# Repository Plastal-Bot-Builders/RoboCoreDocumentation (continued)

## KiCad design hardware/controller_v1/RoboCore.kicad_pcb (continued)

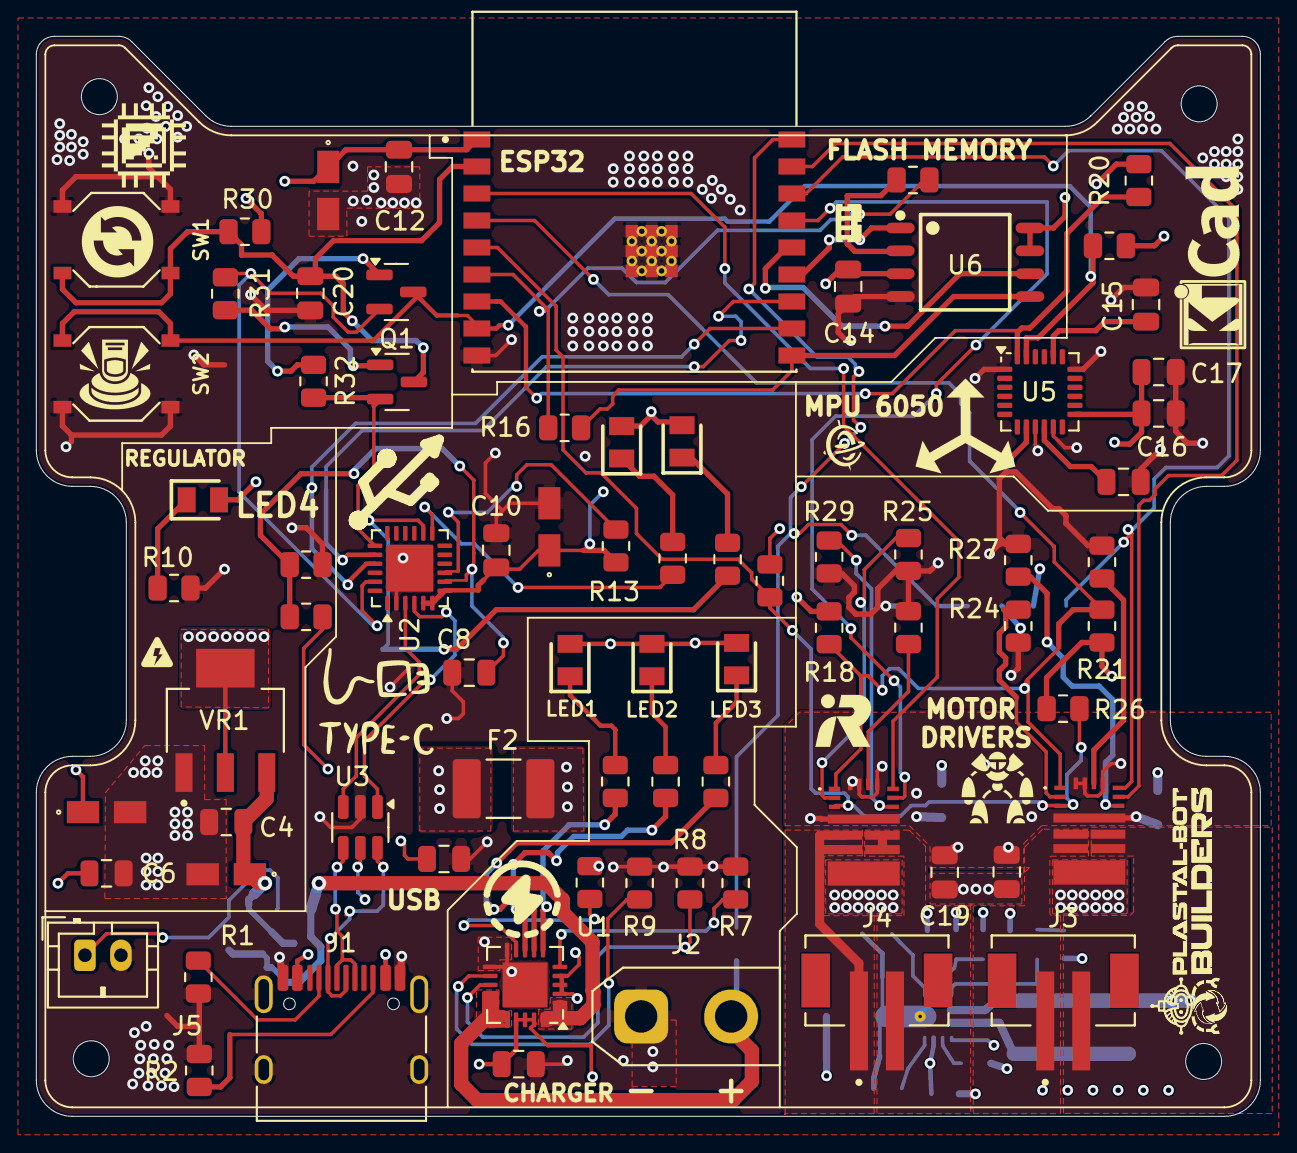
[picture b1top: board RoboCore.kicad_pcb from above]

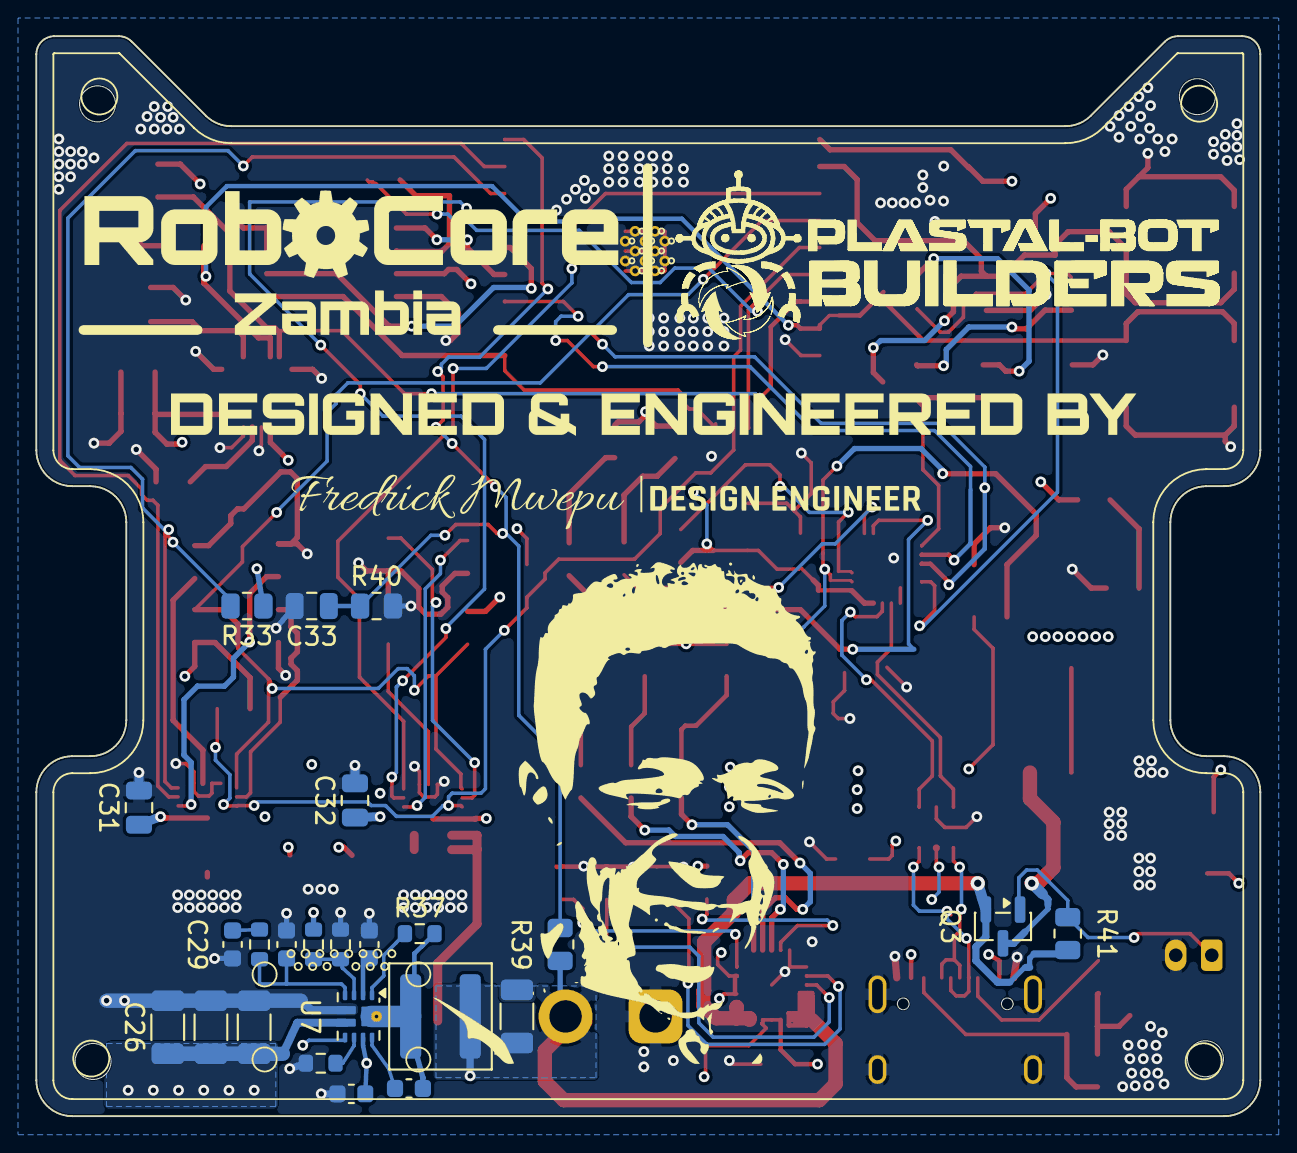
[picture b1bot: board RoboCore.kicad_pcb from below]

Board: 4 copper layers, 68.0 x 60.0 mm, 104 parts (24 on the bottom side), 73 nets.

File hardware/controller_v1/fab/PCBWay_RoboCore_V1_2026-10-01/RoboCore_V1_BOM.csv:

Item,Designators,Qty,Value,Package (KiCad footprint),Manufacturer,Manufacturer Part Number,Rating / sourcing note,Mount,Description
1,"C1,C4,C6,C10,C13,C31,C32,C33",8,0.1µF,C_0805_2012Metric,,,"MLCC X7R ±10%, 50 V",SMD,"capacitor, non-polarized/bipolar"
2,"C2,C8,C14,C20",4,1µF,C_0805_2012Metric,,,"MLCC X7R ±10%, 25 V (16 V min)",SMD,"capacitor, non-polarized/bipolar"
3,"C5,C7,C11",3,10µF,1206 (3216 metric) MLCC on T491A pads,,,"CERAMIC (not tantalum): MLCC 1206 X5R ±10%, 16 V, e.g. Samsung CL31A106KOHNNNE; the T491A footprint pads fit a 1206 part",SMD,Ceramic capacitor (MLCC) 1206 X5R 16V; fits the tantalum A-case (3216) pads
4,C9,1,4.7µF,1206 (3216 metric) MLCC on T491A pads,,,"CERAMIC (not tantalum): MLCC 1206 X5R ±10%, 16 V, e.g. Samsung CL31A475KOHNNNE; the T491A footprint pads fit a 1206 part",SMD,Ceramic capacitor (MLCC) 1206 X5R 16V; fits the tantalum A-case (3216) pads
5,C12,1,4.7µF,C_0805_2012Metric,,,"MLCC X5R/X7R ±10%, 16 V (10 V min)",SMD,"capacitor, non-polarized/bipolar"
6,C15,1,2.2nF,C_0805_2012Metric,,,"MLCC X7R ±10%, 50 V; MPU-6050 charge-pump capacitor, 50 V rating required by the datasheet",SMD,"capacitor, non-polarized/bipolar"
7,"C16,C17",2,2.2µF,C_0805_2012Metric,,,"MLCC X5R/X7R ±10%, 16 V (10 V min)",SMD,"capacitor, non-polarized/bipolar"
8,"C18,C19",2,22µF,C_0805_2012Metric,,,"MLCC X5R ±20%, 16 V; 6 V motor rail; e.g. Samsung CL21A226MOQNNNE",SMD,"capacitor, non-polarized/bipolar"
9,"C22,C24,C25,C26",4,22µF 16V,C_1206_3216Metric,,,"MLCC X5R/X7R, 16 V or higher (25 V keeps more capacitance at 6 V)",SMD,capacitor
10,"C23,C28",2,0.1µF,C_0603_1608Metric,,,"MLCC X7R ±10%, 25 V (16 V min)",SMD,capacitor
11,C27,1,2.2µF,C_0603_1608Metric,,,"MLCC X5R/X7R ±10%, 16 V",SMD,capacitor
12,C29,1,10nF,C_0603_1608Metric,,,"MLCC X7R ±10%, 50 V",SMD,capacitor
13,C30,1,22pF,C_0603_1608Metric,,,"MLCC C0G/NP0 ±5%, 50 V",SMD,capacitor
14,F2,1,Polyfuse,FUSSC324X455X250-2N,,,"PTC resettable fuse, 1812, I_hold 1.5 A, V_max ≥ 6 V, e.g. Bourns MF-MSMF150/24X-2 (MF-MSMF150-2 is obsolete)",SMD,"Resettable fuse, polymeric positive temperature coefficient"
15,"IC1,IC2",2,DRV8245HQRXZRQ1,DRV8245HQRXZRQ1,Texas Instruments,DRV8245HQRXZRQ1,,SMD,"Motor / Motion / Ignition Controllers & Drivers Automotive 40-V, 32-A H-Bridge driver with integrated current sensing and feedback"
16,J1,1,TYPE-C-31-M-12,USB_C_Receptacle_HRO_TYPE-C-31-M-12,Korean Hroparts Elec,TYPE-C-31-M-12,,SMD,"USB 2.0 Type-C receptacle, 16 pin, mid/top mount"
17,J2,1,XT30UPB-M,AMASS_XT30UPB-M_1x02_P5.0mm_Vertical,AMASS,XT30UPB-M,,THT,"Battery input, XT30 male, vertical PCB mount, keyed"
18,J3,1,MOTOR_A,JST_B2B-PH-SM4-TB,JST,B2B-PH-SM4-TB,,SMD,
19,J4,1,MOTOR_B,JST_B2B-PH-SM4-TB,JST,B2B-PH-SM4-TB,,SMD,
20,J5,1,POWER_SW,JST_PH_B2B-PH-K_1x02_P2.00mm_Vertical,JST,B2B-PH-K-S,,THT,External ON/OFF switch (closed = ON); fit a jumper for always-on
21,L1,1,2.2uH,L_Coilcraft_XAL5030-XXX,Coilcraft,XAL5030-222MEC,,SMD,"Boost inductor 2.2 uH, Isat 9.2 A, 14.5 mOhm max"
22,"LED1,LED4,LED6",3,LTST-C170KRKT,LEDC2012X120N,Lite-On,LTST-C170KRKT,,SMD,Standard LEDs - SMD Red Clear 631nm
23,"LED2,LED5",2,LTST-C170GKT,LEDC2012X120N,Lite-On,LTST-C170GKT,,SMD,"LED,SMD,0805,Green,6mcd,130deg Lite-On LTST-C170GKT, CHIPLED 0805 Series Green LED, 569 nm 2012 (0805), Rectangle Lens SMD package"
24,LED3,1,LTST-C170TBKT,LEDC2012X120N,Lite-On,LTST-C170TBKT,,SMD,"LED,SMD,0805,Blue,28mcd,130deg"
25,"Q1,Q2",2,BC817,SOT-23,Nexperia,BC817-40,any BC817 (-16/-25/-40) is fine,SMD,"0.8A Ic, 45V Vce, NPN Transistor, SOT-23"
26,Q3,1,AO3401A,SOT-23,Alpha & Omega,AO3401A,,SMD,Power switch P-MOSFET
27,"R1,R2",2,5.1K,R_0805_2012Metric,,,"Thick film 1%, 1/8 W",SMD,resistor
28,"R3,R4,R5,R10,R14,R15",6,470,R_0805_2012Metric,,,"Thick film 1%, 1/8 W",SMD,resistor
29,"R6,R7,R9,R18,R21,R26,R27,R28,R29,R30,R31,R32,R33",13,10K,R_0805_2012Metric,,,"Thick film 1%, 1/8 W",SMD,"Boot-strap pull-up: GPIO2/DIR_A must read high at reset (DRV824x input pull-down),resistor"
30,"R8,R13,R24,R25",4,1K,R_0805_2012Metric,,,"Thick film 1%, 1/8 W",SMD,resistor
31,R11,1,47K,R_0805_2012Metric,,,"Thick film 1%, 1/8 W",SMD,resistor
32,R12,1,22K,R_0805_2012Metric,,,"Thick film 1%, 1/8 W",SMD,resistor
33,R17,1,50,R_0805_2012Metric,,,"Thick film 1%, 1/8 W; 49.9 Ω acceptable",SMD,resistor
34,"R19,R20",2,4.7K,R_0805_2012Metric,,,"Thick film 1%, 1/8 W",SMD,resistor
35,"R22,R23",2,8.2K,R_0805_2012Metric,,,"Thick film 1%, 1/8 W",SMD,resistor
36,R34,1,9.1K,R_0603_1608Metric,,,Thick film 1% (boost loop compensation),SMD,resistor
37,"R35,R37",2,300K,R_0603_1608Metric,,,"Thick film 1% (sets boost output voltage, switching frequency and current limit; 1% required)",SMD,resistor
38,R36,1,75K,R_0603_1608Metric,,,"Thick film 1% (sets boost output voltage, switching frequency and current limit; 1% required)",SMD,resistor
39,R38,1,200K,R_0603_1608Metric,,,"Thick film 1% (sets boost output voltage, switching frequency and current limit; 1% required)",SMD,resistor
40,"R39,R40,R41",3,100K,R_0805_2012Metric,,,"Thick film 1%, 1/8 W",SMD,resistor
41,SW1,1,RESET,SW4-SMD-5.2X5.2X1.5MM,ALPS,SKQGADE010,,SMD,
42,SW2,1,BOOT,SW4-SMD-5.2X5.2X1.5MM,ALPS,SKQGADE010,,SMD,
43,U1,1,MCP73871,QFN-20-1EP_4x4mm_P0.5mm_EP2.5x2.5mm,Microchip,MCP73871-2CCI/ML,-2 = 4.20 V charge voltage (standard Li-ion),SMD,"Single cell, Li-Ion/Li-Po charge management controller"
44,U2,1,CP2102N-A02-GQFN24,QFN-24-1EP_4x4mm_P0.5mm_EP2.6x2.6mm,Silicon Labs,CP2102N-A02-GQFN24,,SMD,"USB to UART bridge with DTR (auto-program), QFN-24"
45,U3,1,USBLC6-2SC6,SOT-23-6,STMicroelectronics,USBLC6-2SC6,,SMD,"Very low capacitance ESD protection diode, 2 data-line, SOT-23-6"
46,U4,1,ESP32-C3-WROOM-02-H4,MODULE_ESP32-C3-WROOM-02-H4,Espressif Systems,ESP32-C3-WROOM-02-H4,,SMD,
47,U5,1,MPU-6050,InvenSense_QFN-24_4x4mm_P0.5mm,TDK InvenSense,MPU-6050,"Older part, so supply is uncertain: ask PCBWay to confirm genuine stock",SMD,"InvenSense 6-Axis Motion Sensor, Gyroscope, Accelerometer, I2C"
48,U6,1,W25Q32JVSSIQ,SOIC127P790X216-8N,Winbond,W25Q32JVSSIQ,,SMD,
49,U7,1,TPS61089RNRR,Texas_VQFN-RNR0011A-11,Texas Instruments,TPS61089RNRR,,SMD,"6 V motor supply boost, 2.7-12 V in, 7 A switch"
50,VR1,1,TLV1117LV33DCYR,VREG_LM1117MPX-3.3_NOPB,Texas Instruments,TLV1117LV33DCYR,,SMD,"1-A low-dropout regulator, 3.3 V fixed, SOT-223 (pin-compatible with LM1117)"

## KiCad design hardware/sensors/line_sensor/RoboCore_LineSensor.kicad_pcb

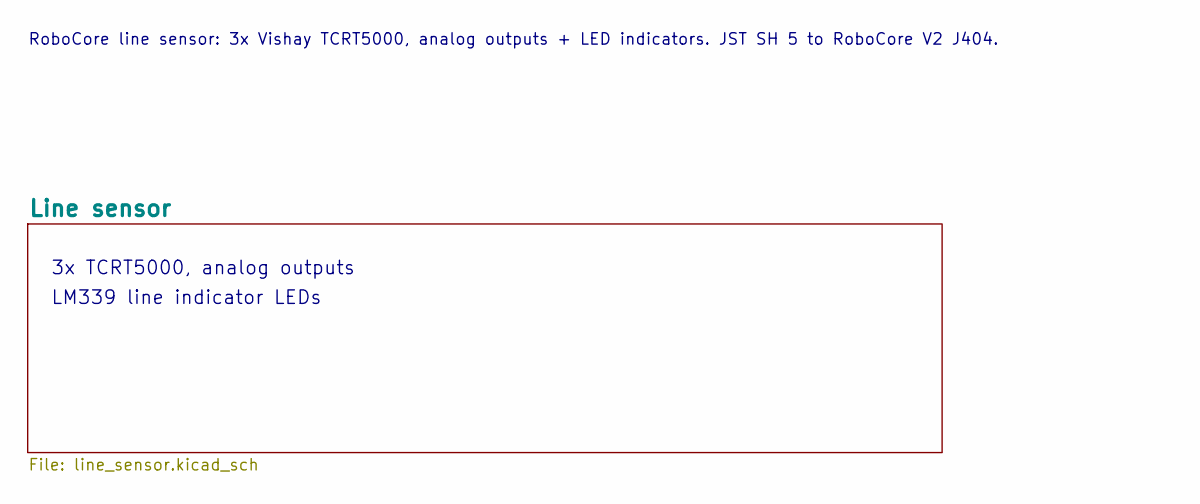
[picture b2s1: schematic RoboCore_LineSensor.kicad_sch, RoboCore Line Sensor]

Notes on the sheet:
3x TCRT5000, analog outputs
LM339 line indicator LEDs
RoboCore line sensor: 3x Vishay TCRT5000, analog outputs + LED indicators. JST SH 5 to RoboCore V2 J404.

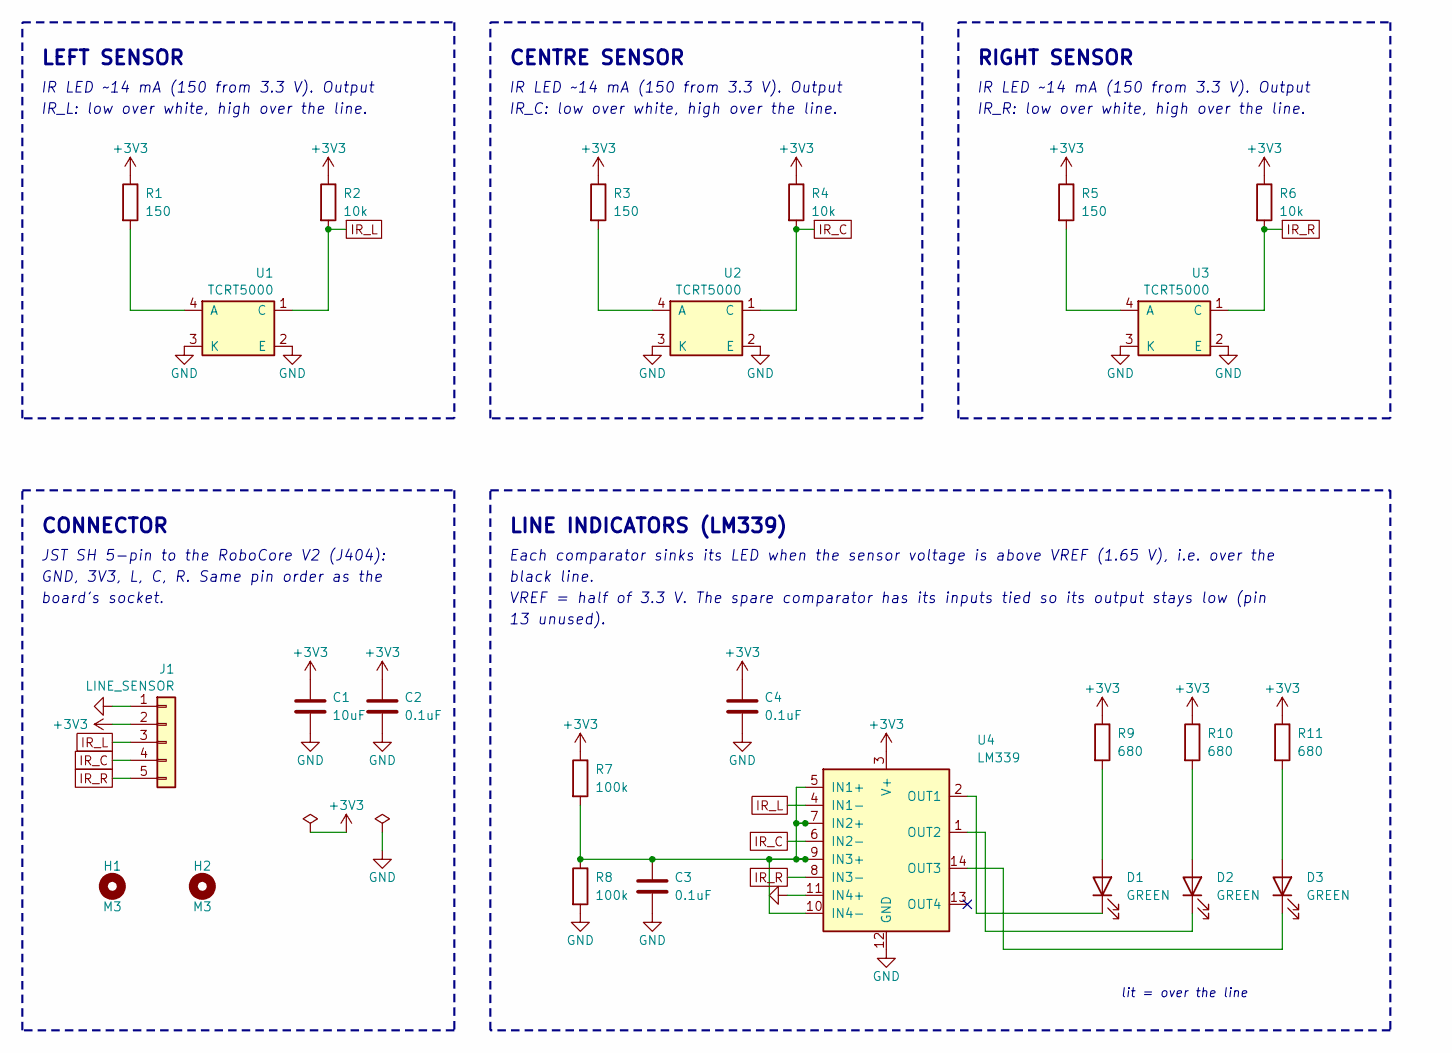
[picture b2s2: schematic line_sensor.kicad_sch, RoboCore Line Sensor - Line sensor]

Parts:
C1: 10uF; C_0805_2012Metric; LCSC C1713
C2, C3, C4: 0.1uF; C_0603_1608Metric; LCSC C1591
D1, D2, D3: GREEN; LED_0603_1608Metric; LCSC C125098
H1, H2: M3; MountingHole_3.2mm_M3
J1: LINE_SENSOR; JST_SH_BM05B-SRSS-TB_1x05-1MP_P1.00mm_Vertical; LCSC C160391
R1, R3, R5: 150; R_0603_1608Metric; LCSC C22808
R2, R4, R6: 10k; R_0603_1608Metric; LCSC C98220
R7, R8: 100k; R_0603_1608Metric; LCSC C25803
R9, R10, R11: 680; R_0603_1608Metric; LCSC C23228
U1, U2, U3: TCRT5000; Vishay_TCRT5000; LCSC C2984661
U4: LM339; SOIC-14_3.9x8.7mm_P1.27mm; LCSC C2829428

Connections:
+3V3: C1.1, C2.1, C4.1, J1.2, R1.1, R2.1, R3.1, R4.1, R5.1, R6.1, R7.1, R9.1, R10.1, R11.1, U4.3 (V+)
GND: C1.2, C2.2, C3.2, C4.2, J1.1, R8.2, U1.2 (E), U1.3 (K), U2.2 (E), U2.3 (K), U3.2 (E), U3.3 (K), U4.11 (IN4+), U4.12 (GND)
IR_C: J1.4, R4.2, U2.1 (C), U4.6 (IN2-)
IR_L: J1.3, R2.2, U1.1 (C), U4.4 (IN1-)
IR_R: J1.5, R6.2, U3.1 (C), U4.8 (IN3-)
unnamed: D1.2 (A), R9.2
unnamed: D1.1 (K), U4.2 (OUT1)
unnamed: D2.2 (A), R10.2
unnamed: D2.1 (K), U4.1 (OUT2)
unnamed: D3.2 (A), R11.2
unnamed: D3.1 (K), U4.14 (OUT3)
unnamed: R1.2, U1.4 (A)
unnamed: R3.2, U2.4 (A)
unnamed: R5.2, U3.4 (A)
unnamed: C3.1, R7.2, R8.1, U4.5 (IN1+), U4.7 (IN2+), U4.9 (IN3+), U4.10 (IN4-)

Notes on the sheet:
LEFT SENSOR
IR LED ~14 mA (150 from 3.3 V). Output
IR_L: low over white, high over the line.
CENTRE SENSOR
IR_C: low over white, high over the line.
RIGHT SENSOR
IR_R: low over white, high over the line.
CONNECTOR
JST SH 5-pin to the RoboCore V2 (J404):
GND, 3V3, L, C, R. Same pin order as the
board's socket.
LINE INDICATORS (LM339)
Each comparator sinks its LED when the sensor voltage is above VREF (1.65 V), i.e. over the
black line.
VREF = half of 3.3 V. The spare comparator has its inputs tied so its output stays low (pin
13 unused).
lit = over the line

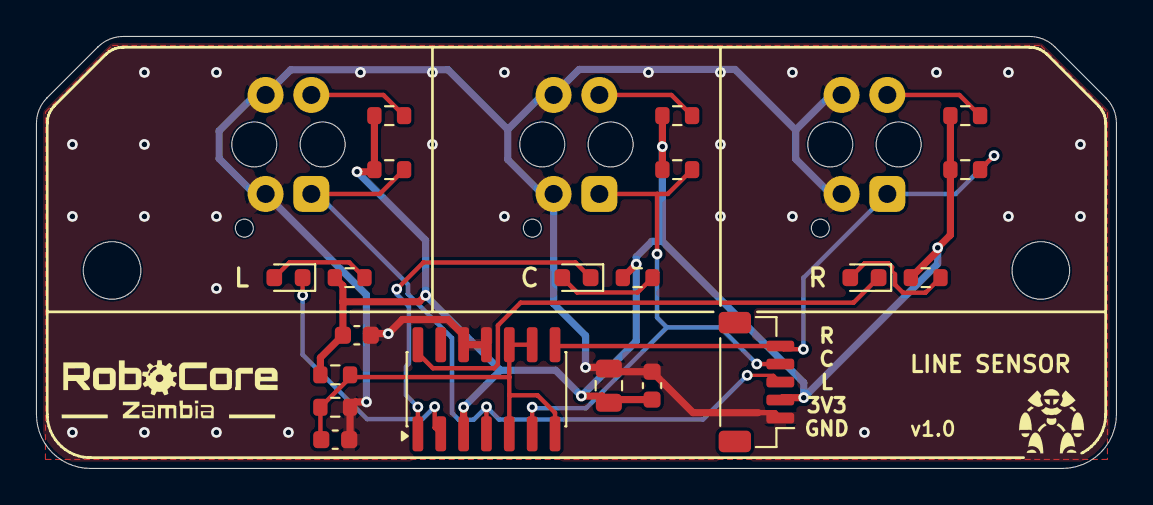
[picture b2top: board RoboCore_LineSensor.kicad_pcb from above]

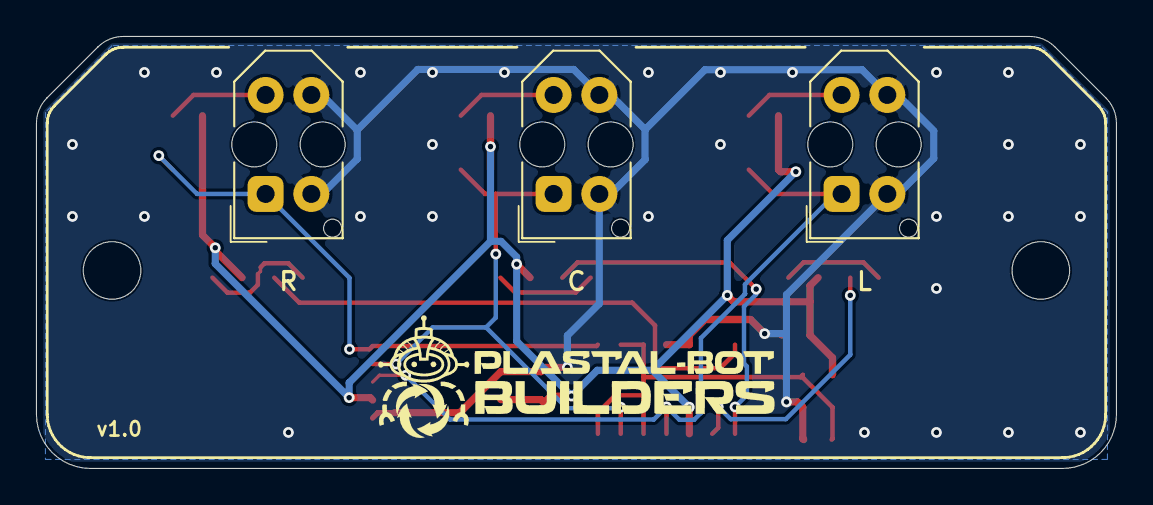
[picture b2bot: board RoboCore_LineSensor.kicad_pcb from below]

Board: 2 copper layers, 60.0 x 24.0 mm, 25 parts (3 on the bottom side), 15 nets.

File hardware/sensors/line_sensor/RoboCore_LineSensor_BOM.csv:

"Refs","Value","Footprint","Manufacturer","MPN","LCSC","Alternative","Qty"
"C1","10uF","Capacitor_SMD:C_0805_2012Metric","","","","","1"
"C2-C4","0.1uF","Capacitor_SMD:C_0603_1608Metric","","","","","3"
"D1-D3","GREEN","LED_SMD:LED_0603_1608Metric","Lite-On","LTST-C191KGKT","C125098","","3"
"J1","LINE_SENSOR","Connector_JST:JST_SH_BM05B-SRSS-TB_1x05-1MP_P1.00mm_Vertical","JST","BM05B-SRSS-TB","C160391","","1"
"R1,R3,R5","150","Resistor_SMD:R_0603_1608Metric","","","","","3"
"R2,R4,R6","10k","Resistor_SMD:R_0603_1608Metric","","","","","3"
"R7,R8","100k","Resistor_SMD:R_0603_1608Metric","","","","","2"
"R9-R11","680","Resistor_SMD:R_0603_1608Metric","","","","","3"
"U1-U3","TCRT5000","OptoDevice:Vishay_TCRT5000","Vishay","TCRT5000","C2984661","TCRT5000L (long leads)","3"
"U4","LM339","Package_SO:SOIC-14_3.9x8.7mm_P1.27mm","JSCJ","LM339","C2829428","TI LM339DR","1"

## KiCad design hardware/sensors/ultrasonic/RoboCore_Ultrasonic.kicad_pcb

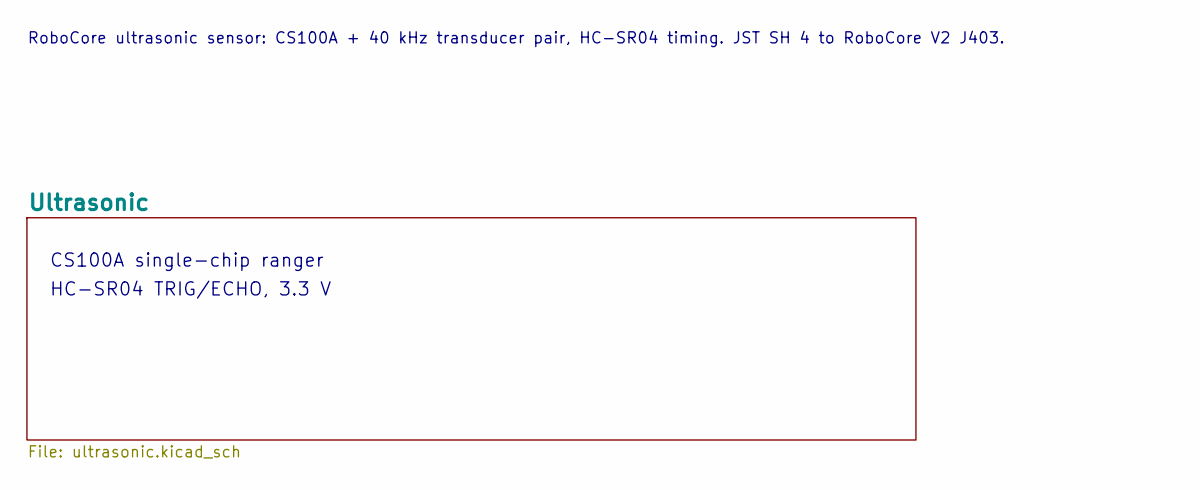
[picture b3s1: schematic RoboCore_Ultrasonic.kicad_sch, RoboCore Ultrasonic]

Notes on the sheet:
CS100A single-chip ranger
HC-SR04 TRIG/ECHO, 3.3 V
RoboCore ultrasonic sensor: CS100A + 40 kHz transducer pair, HC-SR04 timing. JST SH 4 to RoboCore V2 J403.

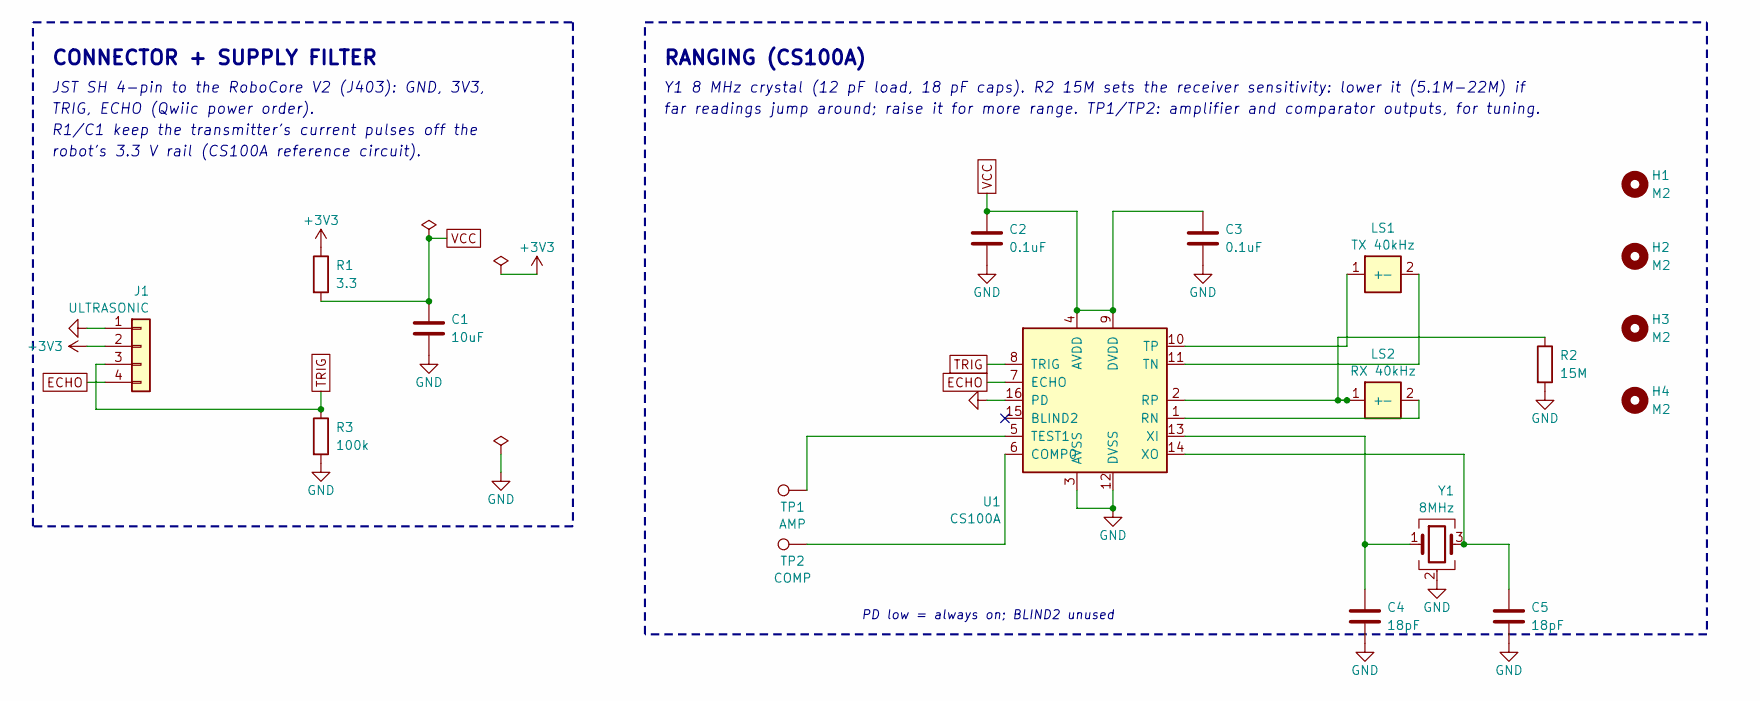
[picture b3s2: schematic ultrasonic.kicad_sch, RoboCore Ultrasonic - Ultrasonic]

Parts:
C1: 10uF; C_0805_2012Metric; LCSC C1713
C2, C3: 0.1uF; C_0603_1608Metric; LCSC C1591
C4, C5: 18pF; C_0603_1608Metric; LCSC C1647
H1, H2, H3, H4: M2; MountingHole_2.2mm_M2
J1: ULTRASONIC; JST_SH_BM04B-SRSS-TB_1x04-1MP_P1.00mm_Vertical; LCSC C160390
LS1: TX 40kHz; Ultrasonic_Transducer_D16.0mm_P10.00mm; LCSC C17701106
LS2: RX 40kHz; Ultrasonic_Transducer_D16.0mm_P10.00mm; LCSC C17701107
R1: 3.3; R_0603_1608Metric; LCSC C137725
R2: 15M; R_0603_1608Metric; LCSC C80615
R3: 100k; R_0603_1608Metric; LCSC C25803
TP1: AMP; TestPoint_Pad_D1.0mm
TP2: COMP; TestPoint_Pad_D1.0mm
U1: CS100A; SOIC-16_3.9x9.9mm_P1.27mm
Y1: 8MHz; Crystal_SMD_3225-4Pin_3.2x2.5mm; LCSC C2842191

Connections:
+3V3: J1.2, R1.1
ECHO: J1.4, U1.7 (ECHO)
GND: C1.2, C2.2, C3.2, C4.2, C5.2, J1.1, R2.2, R3.2, U1.3 (AVSS), U1.12 (DVSS), U1.16 (PD), Y1.2 (G), Y1.4 (G)
unnamed: LS1.1 (+), U1.10 (TP)
unnamed: LS1.2 (-), U1.11 (TN)
unnamed: LS2.1 (+), R2.1, U1.2 (RP)
unnamed: LS2.2 (-), U1.1 (RN)
unnamed: TP2.1, U1.6 (COMP0)
unnamed: TP1.1, U1.5 (TEST1)
unnamed: C4.1, U1.13 (XI), Y1.1
unnamed: C5.1, U1.14 (XO), Y1.3
TRIG: J1.3, R3.1, U1.8 (TRIG)
VCC: C1.1, C2.1, C3.1, R1.2, U1.4 (AVDD), U1.9 (DVDD)

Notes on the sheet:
CONNECTOR + SUPPLY FILTER
JST SH 4-pin to the RoboCore V2 (J403): GND, 3V3,
TRIG, ECHO (Qwiic power order).
R1/C1 keep the transmitter's current pulses off the
robot's 3.3 V rail (CS100A reference circuit).
RANGING (CS100A)
Y1 8 MHz crystal (12 pF load, 18 pF caps). R2 15M sets the receiver sensitivity: lower it (5.1M-22M) if
far readings jump around; raise it for more range. TP1/TP2: amplifier and comparator outputs, for tuning.
PD low = always on; BLIND2 unused

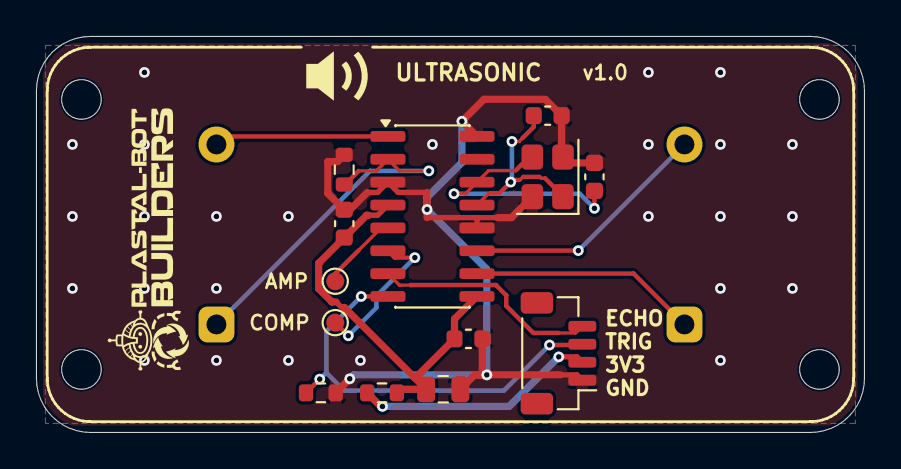
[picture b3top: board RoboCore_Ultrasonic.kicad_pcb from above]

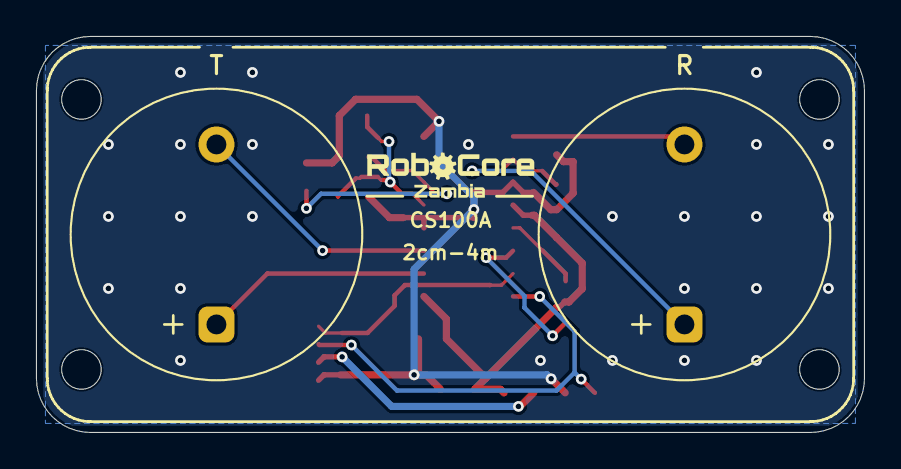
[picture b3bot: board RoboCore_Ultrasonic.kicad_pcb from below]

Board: 2 copper layers, 46.0 x 22.0 mm, 19 parts (2 on the bottom side), 13 nets.

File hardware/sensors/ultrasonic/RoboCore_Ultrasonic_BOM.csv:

"Refs","Value","Footprint","Manufacturer","MPN","LCSC","Alternative","Qty"
"C1","10uF","Capacitor_SMD:C_0805_2012Metric","","","","","1"
"C2,C3","0.1uF","Capacitor_SMD:C_0603_1608Metric","","","","","2"
"C4,C5","18pF","Capacitor_SMD:C_0603_1608Metric","","","","","2"
"J1","ULTRASONIC","Connector_JST:JST_SH_BM04B-SRSS-TB_1x04-1MP_P1.00mm_Vertical","JST","BM04B-SRSS-TB","C160390","","1"
"LS1","TX 40kHz","RoboCoreV2:Ultrasonic_Transducer_D16.0mm_P10.00mm","HYDZ","HY40A16T12-1","C17701106","","1"
"LS2","RX 40kHz","RoboCoreV2:Ultrasonic_Transducer_D16.0mm_P10.00mm","HYDZ","HY40A16R12-1","C17701107","","1"
"R1","3.3","Resistor_SMD:R_0603_1608Metric","","","","","1"
"R2","15M","Resistor_SMD:R_0603_1608Metric","","","","","1"
"R3","100k","Resistor_SMD:R_0603_1608Metric","","","","","1"
"U1","CS100A","Package_SO:SOIC-16_3.9x9.9mm_P1.27mm","Suzhou ShunGuiZhiLian (100sensor.com)","CS100A","","not at LCSC: buy from AliExpress/Alibaba and consign to the assembler","1"
"Y1","8MHz","Crystal:Crystal_SMD_3225-4Pin_3.2x2.5mm","HCI","XC32M4-8.000-F12LJDT","C2842191","","1"

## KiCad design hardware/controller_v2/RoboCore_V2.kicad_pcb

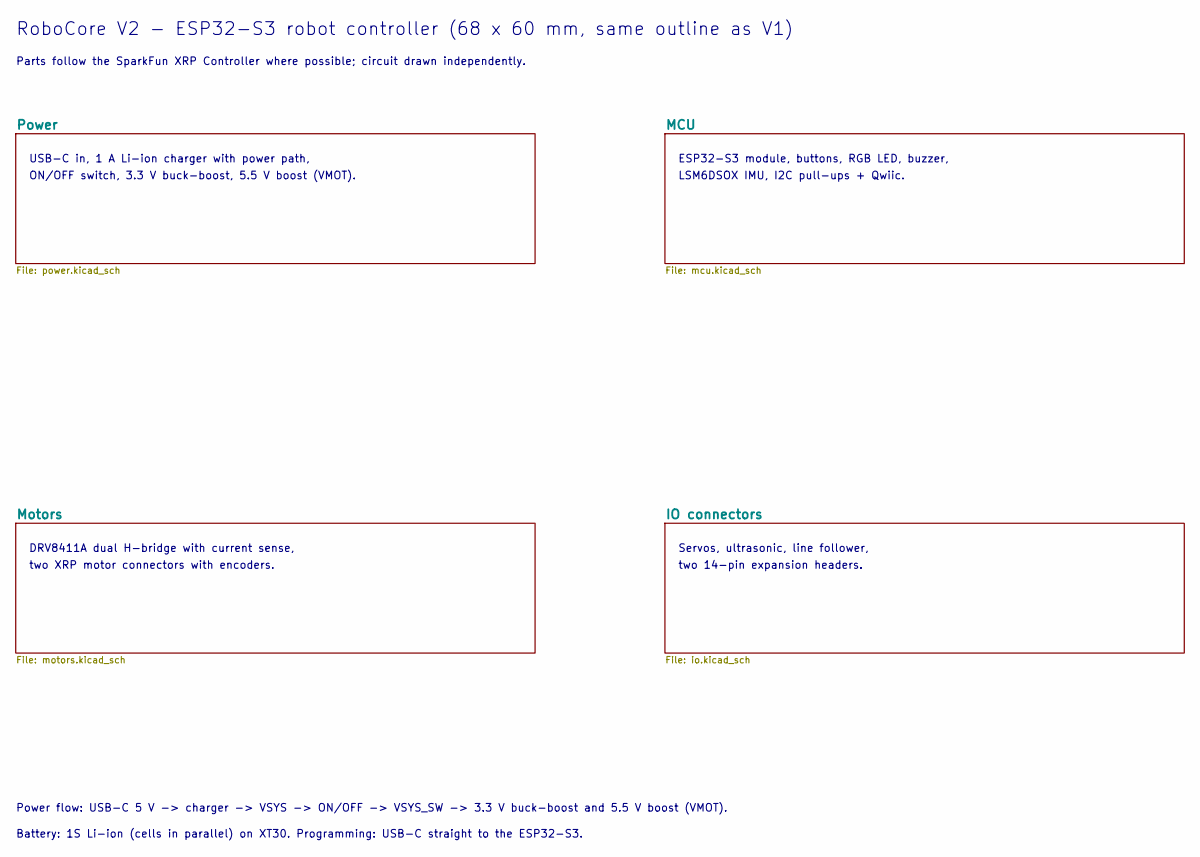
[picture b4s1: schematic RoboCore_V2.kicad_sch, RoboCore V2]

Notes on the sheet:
USB-C in, 1 A Li-ion charger with power path,
ON/OFF switch, 3.3 V buck-boost, 5.5 V boost (VMOT).
ESP32-S3 module, buttons, RGB LED, buzzer,
LSM6DSOX IMU, I2C pull-ups + Qwiic.
DRV8411A dual H-bridge with current sense,
two XRP motor connectors with encoders.
Servos, ultrasonic, line follower,
two 14-pin expansion headers.
RoboCore V2 - ESP32-S3 robot controller (68 x 60 mm, same outline as V1)
Parts follow the SparkFun XRP Controller where possible; circuit drawn independently.
Power flow: USB-C 5 V -> charger -> VSYS -> ON/OFF -> VSYS_SW -> 3.3 V buck-boost and 5.5 V boost (VMOT).
Battery: 1S Li-ion (cells in parallel) on XT30. Programming: USB-C straight to the ESP32-S3.
